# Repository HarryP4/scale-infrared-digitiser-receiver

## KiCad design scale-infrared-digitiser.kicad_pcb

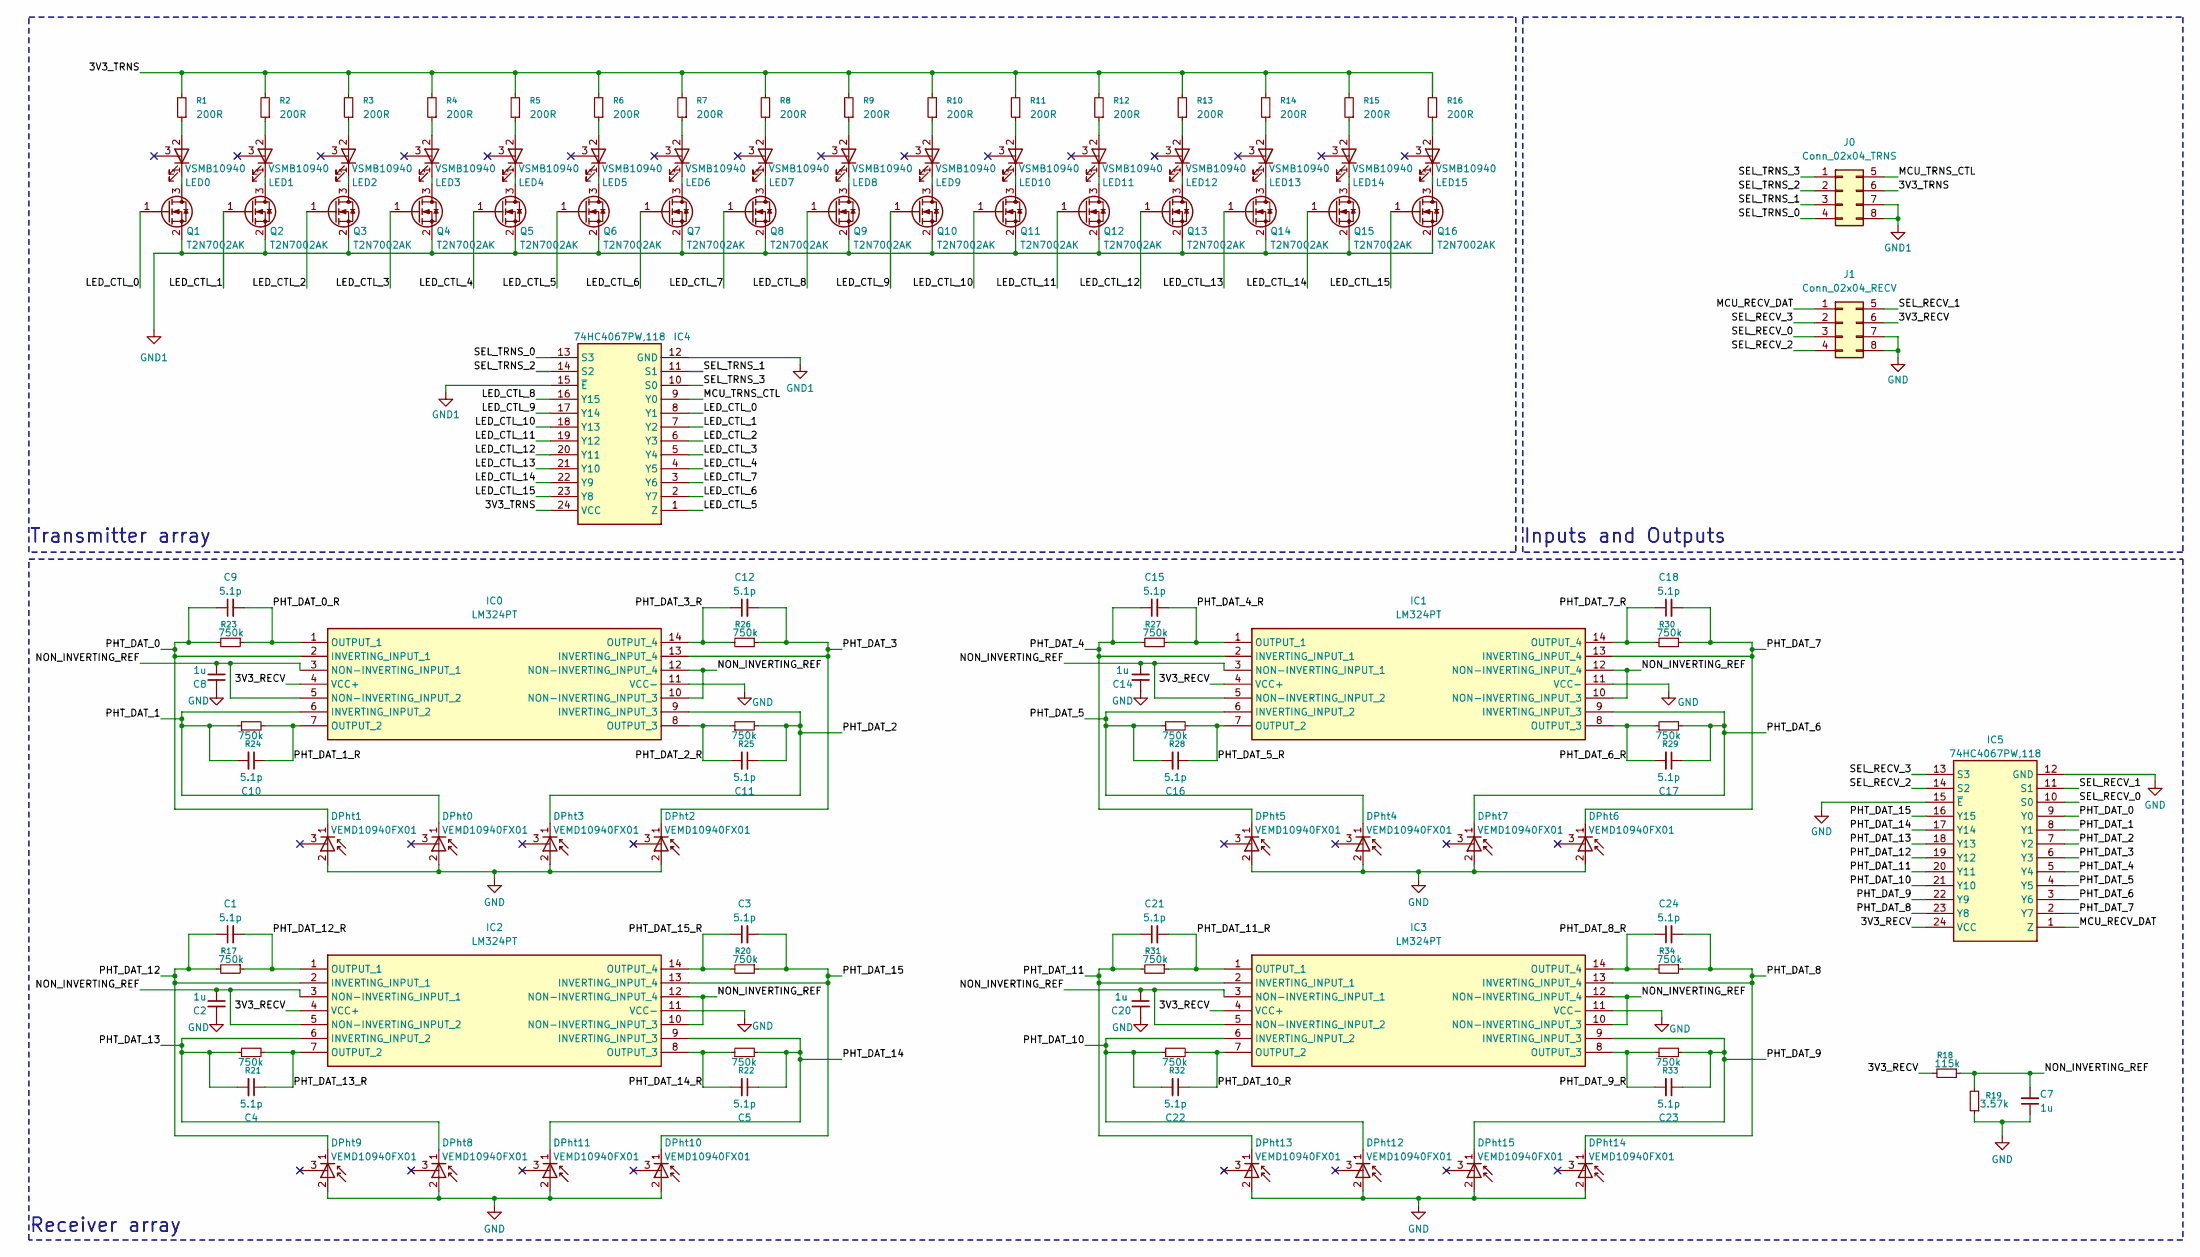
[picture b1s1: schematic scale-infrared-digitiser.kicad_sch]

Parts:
C1, C3, C4, C5, C9, C10, C11, C12, C15, C16, C17, C18, C21, C22, C23, C24: 5.1p; C_0603_1608Metric; LCSC C3882846
C2, C7, C8, C14, C20: 1u; C_0603_1608Metric; LCSC C106214
DPht0, DPht1, DPht2, DPht3, DPht4, DPht5, DPht6, DPht7, DPht8, DPht9, DPht10, DPht11, DPht12, DPht13, DPht14, DPht15: VEMD10940FX01; Manufacturer_Part_Number VEMD10940FX01; Mouser Part Number 78-VEMD10940FX01
IC0, IC1, IC2, IC3: LM324PT; SOP65P640X120-14N; Manufacturer_Part_Number LM324PT; Mouser Part Number 511-LM324P
IC4, IC5: 74HC4067PW,118; SOP65P640X110-24N; Manufacturer_Part_Number 74HC4067PW,118; Mouser Part Number 771-74HC4067PW-T
J0: Conn_02x04_TRNS; PinHeader_2x04_P2.54mm_Vertical
J1: Conn_02x04_RECV; PinHeader_2x04_P2.54mm_Vertical
LED0, LED1, LED2, LED3, LED4, LED5, LED6, LED7, LED8, LED9, LED10, LED11, LED12, LED13, LED14, LED15: VSMB10940; Manufacturer_Part_Number VSMB10940; Mouser Part Number 78-VSMB10940
Q1, Q2, Q3, Q4, Q5, Q6, Q7, Q8, Q9, Q10, Q11, Q12, Q13, Q14, Q15, Q16: T2N7002AK; SOT-23; LCSC C5224226
R1, R2, R3, R4, R5, R6, R7, R8, R9, R10, R11, R12, R13, R14, R15, R16: 200R; R_0603_1608Metric; LCSC C863359
R17, R20, R21, R22, R23, R24, R25, R26, R27, R28, R29, R30, R31, R32, R33, R34: 750k; R_0603_1608Metric; LCSC C863934
R18: 115k; R_0603_1608Metric; LCSC C217699
R19: 3.57k; R_0603_1608Metric; LCSC C218009

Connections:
/3V3_RECV: IC0.4 (VCC+), IC1.4 (VCC+), IC2.4 (VCC+), IC3.4 (VCC+), IC5.24 (VCC), J1.6, R18.2
/3V3_TRNS: IC4.24 (VCC), J0.6, R1.2, R2.2, R3.2, R4.2, R5.2, R6.2, R7.2, R8.2, R9.2, R10.2, R11.2, R12.2, R13.2, R14.2, R15.2, R16.2
/LED_CTL_0: IC4.8 (Y1), Q1.1 (G)
/LED_CTL_1: IC4.7 (Y2), Q2.1 (G)
/LED_CTL_2: IC4.6 (Y3), Q3.1 (G)
/LED_CTL_3: IC4.5 (Y4), Q4.1 (G)
/LED_CTL_4: IC4.4 (Y5), Q5.1 (G)
/LED_CTL_5: IC4.1 (Z), Q6.1 (G)
/LED_CTL_6: IC4.2 (Y7), Q7.1 (G)
/LED_CTL_7: IC4.3 (Y6), Q8.1 (G)
/LED_CTL_8: IC4.16 (Y15), Q9.1 (G)
/LED_CTL_9: IC4.17 (Y14), Q10.1 (G)
/LED_CTL_10: IC4.18 (Y13), Q11.1 (G)
/LED_CTL_11: IC4.19 (Y12), Q12.1 (G)
/LED_CTL_12: IC4.20 (Y11), Q13.1 (G)
/LED_CTL_13: IC4.21 (Y10), Q14.1 (G)
/LED_CTL_14: IC4.22 (Y9), Q15.1 (G)
/LED_CTL_15: IC4.23 (Y8), Q16.1 (G)
/MCU_RECV_DAT: IC5.1 (Z), J1.1
/MCU_TRNS_CTL: IC4.9 (Y0), J0.5
/NON_INVERTING_REF: C2.1, C7.2, C8.1, C14.1, C20.1, IC0.3 (NON-INVERTING_INPUT_1), IC0.5 (NON-INVERTING_INPUT_2), IC0.10 (NON-INVERTING_INPUT_3), IC0.12 (NON-INVERTING_INPUT_4), IC1.3 (NON-INVERTING_INPUT_1), IC1.5 (NON-INVERTING_INPUT_2), IC1.10 (NON-INVERTING_INPUT_3), IC1.12 (NON-INVERTING_INPUT_4), IC2.3 (NON-INVERTING_INPUT_1), IC2.5 (NON-INVERTING_INPUT_2), IC2.10 (NON-INVERTING_INPUT_3), IC2.12 (NON-INVERTING_INPUT_4), IC3.3 (NON-INVERTING_INPUT_1), IC3.5 (NON-INVERTING_INPUT_2), IC3.10 (NON-INVERTING_INPUT_3), IC3.12 (NON-INVERTING_INPUT_4), R18.1, R19.2
/PHT_DAT_0: C9.1, DPht1.1 (K), IC0.2 (INVERTING_INPUT_1), IC5.9 (Y0), R23.2
/PHT_DAT_0_R: C9.2, IC0.1 (OUTPUT_1), R23.1
/PHT_DAT_1: C10.2, DPht0.1 (K), IC0.6 (INVERTING_INPUT_2), IC5.8 (Y1), R24.1
/PHT_DAT_1_R: C10.1, IC0.7 (OUTPUT_2), R24.2
/PHT_DAT_2: C11.1, DPht3.1 (K), IC0.9 (INVERTING_INPUT_3), IC5.7 (Y2), R25.2
/PHT_DAT_2_R: C11.2, IC0.8 (OUTPUT_3), R25.1
/PHT_DAT_3: C12.2, DPht2.1 (K), IC0.13 (INVERTING_INPUT_4), IC5.6 (Y3), R26.1
/PHT_DAT_3_R: C12.1, IC0.14 (OUTPUT_4), R26.2
/PHT_DAT_4: C15.1, DPht5.1 (K), IC1.2 (INVERTING_INPUT_1), IC5.5 (Y4), R27.2
/PHT_DAT_4_R: C15.2, IC1.1 (OUTPUT_1), R27.1
/PHT_DAT_5: C16.2, DPht4.1 (K), IC1.6 (INVERTING_INPUT_2), IC5.4 (Y5), R28.1
/PHT_DAT_5_R: C16.1, IC1.7 (OUTPUT_2), R28.2
/PHT_DAT_6: C17.1, DPht7.1 (K), IC1.9 (INVERTING_INPUT_3), IC5.3 (Y6), R29.2
/PHT_DAT_6_R: C17.2, IC1.8 (OUTPUT_3), R29.1
/PHT_DAT_7: C18.2, DPht6.1 (K), IC1.13 (INVERTING_INPUT_4), IC5.2 (Y7), R30.1
/PHT_DAT_7_R: C18.1, IC1.14 (OUTPUT_4), R30.2
/PHT_DAT_8: C24.2, DPht14.1 (K), IC3.13 (INVERTING_INPUT_4), IC5.23 (Y8), R34.1
/PHT_DAT_8_R: C24.1, IC3.14 (OUTPUT_4), R34.2
/PHT_DAT_9: C23.1, DPht15.1 (K), IC3.9 (INVERTING_INPUT_3), IC5.22 (Y9), R33.2
/PHT_DAT_9_R: C23.2, IC3.8 (OUTPUT_3), R33.1
/PHT_DAT_10: C22.2, DPht12.1 (K), IC3.6 (INVERTING_INPUT_2), IC5.21 (Y10), R32.1
/PHT_DAT_10_R: C22.1, IC3.7 (OUTPUT_2), R32.2
/PHT_DAT_11: C21.1, DPht13.1 (K), IC3.2 (INVERTING_INPUT_1), IC5.20 (Y11), R31.2
/PHT_DAT_11_R: C21.2, IC3.1 (OUTPUT_1), R31.1
/PHT_DAT_12: C1.1, DPht9.1 (K), IC2.2 (INVERTING_INPUT_1), IC5.19 (Y12), R17.2
/PHT_DAT_12_R: C1.2, IC2.1 (OUTPUT_1), R17.1
/PHT_DAT_13: C4.2, DPht8.1 (K), IC2.6 (INVERTING_INPUT_2), IC5.18 (Y13), R21.1
/PHT_DAT_13_R: C4.1, IC2.7 (OUTPUT_2), R21.2
/PHT_DAT_14: C5.1, DPht11.1 (K), IC2.9 (INVERTING_INPUT_3), IC5.17 (Y14), R22.2
/PHT_DAT_14_R: C5.2, IC2.8 (OUTPUT_3), R22.1
/PHT_DAT_15: C3.2, DPht10.1 (K), IC2.13 (INVERTING_INPUT_4), IC5.16 (Y15), R20.1
/PHT_DAT_15_R: C3.1, IC2.14 (OUTPUT_4), R20.2
/SEL_RECV_0: IC5.10 (S0), J1.3
/SEL_RECV_1: IC5.11 (S1), J1.5
/SEL_RECV_2: IC5.14 (S2), J1.4
/SEL_RECV_3: IC5.13 (S3), J1.2
/SEL_TRNS_0: IC4.13 (S3), J0.4
/SEL_TRNS_1: IC4.11 (S1), J0.3
/SEL_TRNS_2: IC4.14 (S2), J0.2
/SEL_TRNS_3: IC4.10 (S0), J0.1
GND: C2.2, C7.1, C8.2, C14.2, C20.2, DPht0.2 (A), DPht1.2 (A), DPht2.2 (A), DPht3.2 (A), DPht4.2 (A), DPht5.2 (A), DPht6.2 (A), DPht7.2 (A), DPht8.2 (A), DPht9.2 (A), DPht10.2 (A), DPht11.2 (A), DPht12.2 (A), DPht13.2 (A), DPht14.2 (A), DPht15.2 (A), IC0.11 (VCC-), IC1.11 (VCC-), IC2.11 (VCC-), IC3.11 (VCC-), IC5.12 (GND), IC5.15 (~E), J1.7, J1.8, R19.1
GND1: IC4.12 (GND), IC4.15 (~E), J0.7, J0.8, Q1.2 (S), Q2.2 (S), Q3.2 (S), Q4.2 (S), Q5.2 (S), Q6.2 (S), Q7.2 (S), Q8.2 (S), Q9.2 (S), Q10.2 (S), Q11.2 (S), Q12.2 (S), Q13.2 (S), Q14.2 (S), Q15.2 (S), Q16.2 (S)
unnamed: LED0.2 (A), R1.1
unnamed: LED0.1 (K), Q1.3 (D)
unnamed: LED1.2 (A), R2.1
unnamed: LED1.1 (K), Q2.3 (D)
unnamed: LED2.2 (A), R3.1
unnamed: LED2.1 (K), Q3.3 (D)
unnamed: LED3.2 (A), R4.1
unnamed: LED3.1 (K), Q4.3 (D)
unnamed: LED4.2 (A), R5.1
unnamed: LED4.1 (K), Q5.3 (D)
unnamed: LED5.2 (A), R6.1
unnamed: LED5.1 (K), Q6.3 (D)
unnamed: LED6.2 (A), R7.1
unnamed: LED6.1 (K), Q7.3 (D)
unnamed: LED7.2 (A), R8.1
unnamed: LED7.1 (K), Q8.3 (D)
unnamed: LED8.2 (A), R9.1
unnamed: LED8.1 (K), Q9.3 (D)
unnamed: LED9.2 (A), R10.1
unnamed: LED9.1 (K), Q10.3 (D)
unnamed: LED10.2 (A), R11.1
unnamed: LED10.1 (K), Q11.3 (D)
unnamed: LED11.2 (A), R12.1
unnamed: LED11.1 (K), Q12.3 (D)
unnamed: LED12.2 (A), R13.1
unnamed: LED12.1 (K), Q13.3 (D)
unnamed: LED13.2 (A), R14.1
unnamed: LED13.1 (K), Q14.3 (D)
unnamed: LED14.2 (A), R15.1
unnamed: LED14.1 (K), Q15.3 (D)
unnamed: LED15.2 (A), R16.1
unnamed: LED15.1 (K), Q16.3 (D)

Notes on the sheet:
Inputs and Outputs
Receiver array
Transmitter array

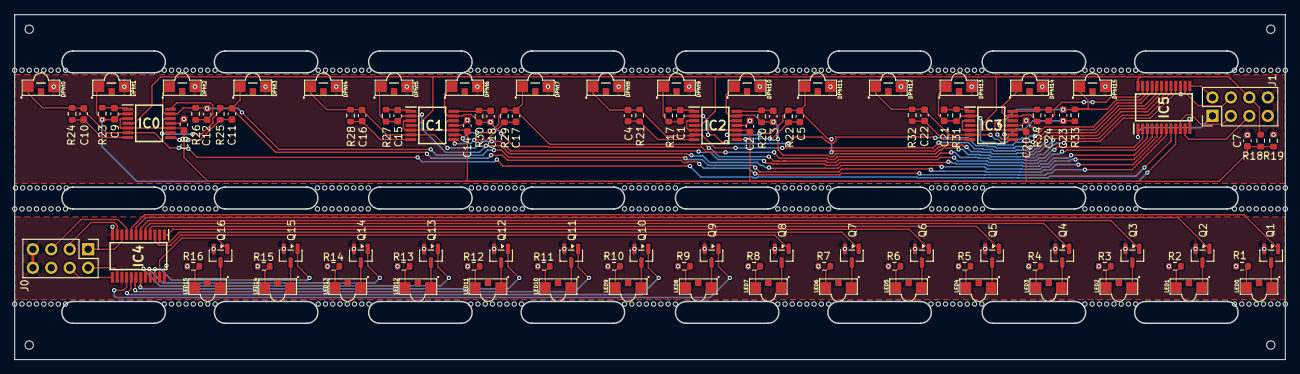
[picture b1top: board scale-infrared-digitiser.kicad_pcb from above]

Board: 2 copper layers, 175.0 x 47.5 mm, 111 parts (0 on the bottom side), 95 nets.

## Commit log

2025-09-04 init
2025-09-09 schematic design completed
2025-09-15 short sides almost complete
2025-09-16 laptop work
2025-09-29 reworking PCB for new dimensions
2025-10-01 completed design ready for review before assembly
2025-10-03 finalised for production
2025-10-08 revised DFM submitted to JLCPCB
2025-11-05 added exports
2025-11-05 modified tags for debugging
2025-11-05 modifying prototype
2025-11-05 start of receiver rework
2025-11-10 reworking to exclude amplifiers - may need to rollback
2025-11-13 Revert "start of receiver rework"
    This reverts commit 024a18523ffd7aae6bd301d38a1d93694bafd7d1.
2025-11-13 reconfigure project structure
2025-11-28 working on updated receiver pcb
